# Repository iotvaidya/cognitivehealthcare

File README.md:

#cognitivehealthcare
##Building cognitive healthcare solutions to rural areas.

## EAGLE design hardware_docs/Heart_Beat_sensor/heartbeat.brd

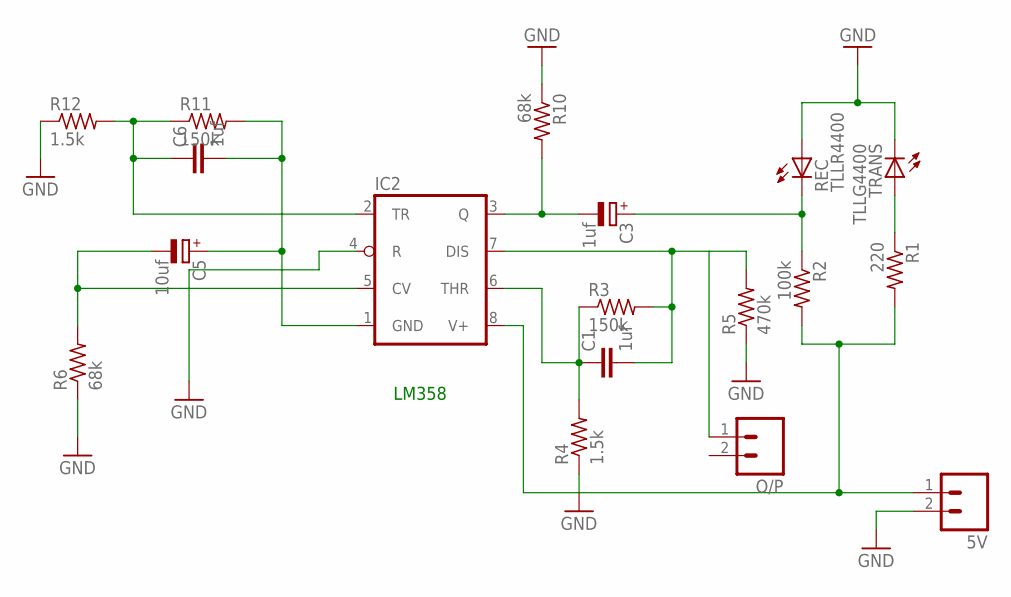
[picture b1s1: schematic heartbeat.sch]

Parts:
5V: M02; 02P
C1, C6: 1uf; C025-030X050
C3: 1uf; TT2D4
C5: 10uf; TT2D4
IC2: LM555N; DIL08-ROUND
O/P: M02; 02P
R1: 220; 0207/10
R2: 100k; 0207/10
R3, R11: 150k; 0207/10
R4, R12: 1.5k; 0207/10
R5: 470k; 0207/10
R6, R10: 68k; 0207/10
REC: TLLR4400; LED3MM
TRANS: TLLG4400; LED3MM

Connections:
GND: 5V.2, IC2.4 (R), R4.1, R5.1, R6.1, R10.1, R12.1, REC.A, TRANS.K (C)
unnamed: R1.1, TRANS.A
unnamed: C3.+, R2.1, REC.K (C)
unnamed: C1.1, IC2.6 (THR), R3.1, R4.2
unnamed: 5V.1, IC2.8 (V+), R1.2, R2.2
unnamed: C3.-, IC2.3 (Q), R10.2
unnamed: C1.2, IC2.7 (DIS), O/P.1, R3.2, R5.2
unnamed: C5.-, IC2.5 (CV), R6.2
unnamed: C6.1, IC2.2 (TR), R11.1, R12.2
unnamed: C5.+, C6.2, IC2.1 (GND), R11.2

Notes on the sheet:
LM358

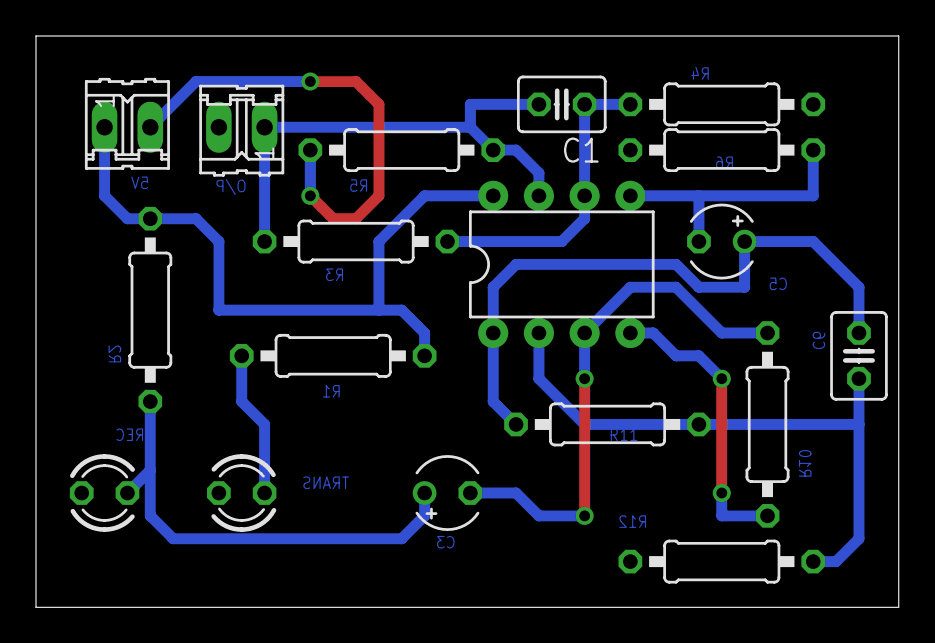
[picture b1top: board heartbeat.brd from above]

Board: 2 copper layers, 47.9 x 31.7 mm, 18 parts (0 on the bottom side), 10 nets.

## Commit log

2016-06-13 Add pulse sensor arduino code for Genuino 101.
    Use this library in the arduino code : https://github.com/bneedhamia/PulseSensorBPM
    For visualisation, find processing code here : https://github.com/WorldFamousElectronics/PulseSensor_Amped_Processing_Visualizer
2016-06-13 Add pulse sensor - genuino interface code.
2016-06-24 Add example code for BLE read using python
    pip install gattlib ----> for using the example
    dependencies :
    pkg-config
    libboost-python-dev
    libboost-thread-dev
    libbluetooth-dev >= 4.101
2016-06-24 Bio_medical Sensors
2016-07-05 Chat Application Connecting Dell gateway to Intel Edison
2016-07-07 Add ecg-anomaly-detection
2016-07-07 Add ECG-Anomaly images
2016-07-09 ECG_Source_Code
2016-07-12 Add iot-vaidya-cloud
2016-07-17 Add gateway publisher code
2016-07-19 Update_1.1
2016-07-19 Update-1.1
